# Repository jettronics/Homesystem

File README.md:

# Homesystem

## Introduction
The Homesystem project has been created to provide web radio stream for different rooms. Which can be controlled by Alexa, by Smart Phone and by a Remote controller centrally.
Further more the Homesystem acts as an Alarm center to monitor different sensors like water sensor to protect for water damage. In case of an Alarm the Homesystem can send Push Messages to a Smart Phone.

## Overview
The Homesystem centeral unit is realized by a Raspberry PI 3B+ controller module. 

Radio can be played by Loudspeakers installed in different rooms of the appartment. Controlling the radio streams can be happened by different ways
* Alexa - The speech command for radio streaming is routed over Alexa to the Central unit. 
* Smart Phone - A browser interface is provided by NodeRED
* Remote Controller - A FM based controller to control the radio player on Central unit.

With the MPD (Music Player Daemon) player running on Central unit a list of radio streaming provides can be selected.  
Sensors detect water flowing accidentally on floor. Sensor Alarm messages are routed by a FM (433MHz) link between Sensor and Central unit.
In case of water detection push messages will be sent which can be received and read on Smartphone.
For further technical details see Wiki page.
## Operation
The User can interact with the Homesystem over Alexa Speech Commands, Smart Phone Interface and Remote Controller.
### Alexa Speech Commands
Node RED uses amazon-echo-device-nodes to receive speech commands from Alexa. For Alexa those nodes are visible as a Light Bulb and can be speech controlled accordingly.
Following Speech Commands are available:
* Radio Küche
* Radio Bad
* Lieblingssender
* Was anderes
* Radio lauter
* Radio leiser

To activate webradio in kitchen say e.g. "Alexa, schalte Radio Küche ein!"
### Smart Phone Interface
There are two tabs as Interface to Homesystem.  
The first one is to control Webradio with different stations.  

The next tab shows the status of the different Watersensors.  

Green LED means no water detected. Red LED means water detected. In case of Water detection a Push message will be sent to Smart Phone.
### Remote Controller
The Remote Controller is a small device to control Webradio by 4 buttons.
* On/Off Webradio
* Next Webradio station
* Volume up
* Volume down
  
### Water Detection
This sensor device detects water and sends an appropiate signal to Homesystem centrals unit. 
The Homesystem acts as a gateway and sends push messages on registered Smart phones in case of water detected. 
The sensor draws very less standby current so that the battery can be used a very long time.

## Improvements
- [x] HF Transmission for Remote Controller just Parity Bit checked. For more robust transmission a CRC check or similiar check can be used.
- [x] Loud speaker announcement for the Webradio channel when changing the Webradio channel over e.g. Speech commands.

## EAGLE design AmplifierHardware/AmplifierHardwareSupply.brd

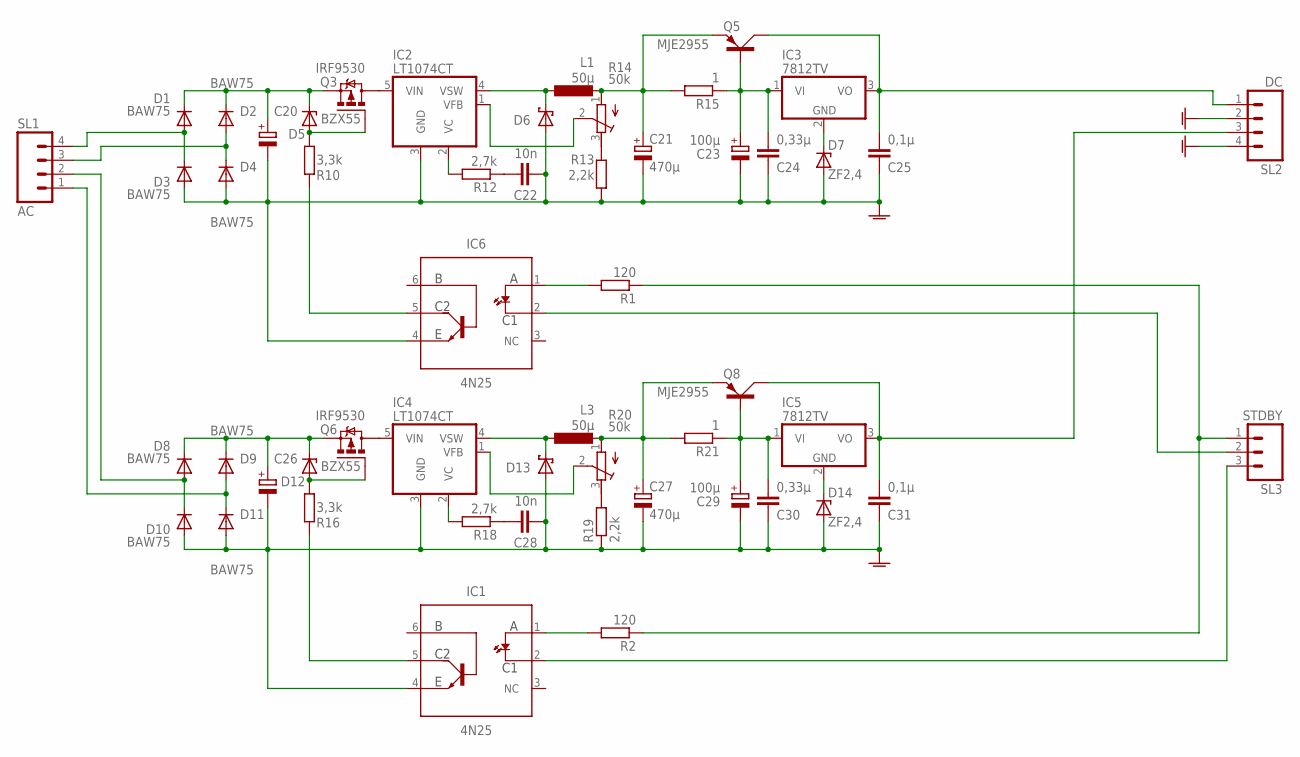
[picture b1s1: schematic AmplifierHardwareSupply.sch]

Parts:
C20, C26: CPOL-EUE5-10.5; E5-10,5
C21, C27: 470µ; E5-10,5
C22, C28: 10n; C025-024X044
C23, C29: 100µ; E5-10,5
C24, C30: 0,33µ; C025-024X044
C25, C31: 0,1µ; C025-024X044
D1, D2, D3, D4, D8, D9, D10, D11: BAW75; DO35-10
D5, D12: BZX55; DO35Z10
D6, D13: SCHOTTKY-DIODEDO35-7; DO35-7
D7, D14: ZF2,4; DO34Z7
IC1, IC6: 4N25; DIP762W60P254L712H480Q6B
IC2, IC4: LT1074CT; TO220-5
IC3, IC5: 7812TV; TO220V
L1, L3: 50µ; TJ3-U1
Q3, Q6: IRF9530; TO220BV
Q5, Q8: MJE2955; TO220AV
R1, R2: 120; 0207/2V
R10, R16: 3,3k; 0207/2V
R12, R18: 2,7k; 0207/2V
R13, R19: 2,2k; 0207/2V
R14, R20: 50k; RTRIM64W
R15, R21: 1; 0207/2V
SL1: AC; 04P
SL2: DC; 04P
SL3: STDBY; 03P

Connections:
+UB2: C31.2, IC5.3 (VO), Q8.C, SL2.3
AGND: C20.-, C21.-, C22.2, C23.-, C24.1, C25.1, C26.-, C27.-, C28.2, C29.-, C30.1, C31.1, D3.A, D4.A, D6.A, D7.A, D10.A, D11.A, D13.A, D14.A, IC1.4 (E), IC2.3 (GND), IC4.3 (GND), IC6.4 (E), R13.1, R19.1, SL2.2, SL2.4
unnamed: C25.2, IC3.3 (VO), Q5.C, SL2.1
unnamed: R1.1, R2.1, SL3.1
unnamed: IC6.1 (A), R1.2
unnamed: IC1.1 (A), R2.2
unnamed: IC6.2 (C1), SL3.2
unnamed: IC1.2 (C1), SL3.3
unnamed: IC2.2 (VC), R12.2
unnamed: R13.2, R14.3 (A)
unnamed: D1.A, D3.C, SL1.4
unnamed: IC4.2 (VC), R18.2
unnamed: IC2.5 (VIN), Q3.D
unnamed: D5.A, Q3.G, R10.2
unnamed: IC6.5 (C2), R10.1
unnamed: C21.+, L1.2, Q5.E, R14.1 (E), R15.2
unnamed: C22.1, R12.1
unnamed: D6.C, IC2.4 (VSW), L1.1
unnamed: IC2.1 (VFB), R14.2 (S)
unnamed: D7.C, IC3.2 (GND)
unnamed: R19.2, R20.3 (A)
unnamed: C23.+, C24.2, IC3.1 (VI), Q5.B, R15.1
unnamed: D8.A, D10.C, SL1.2
unnamed: D9.A, D11.C, SL1.1
unnamed: C26.+, D8.C, D9.C, D12.C, Q6.S
unnamed: D12.A, Q6.G, R16.2
unnamed: IC1.5 (C2), R16.1
unnamed: C28.1, R18.1
unnamed: D13.C, IC4.4 (VSW), L3.1
unnamed: IC4.5 (VIN), Q6.D
unnamed: C27.+, L3.2, Q8.E, R20.1 (E), R21.2
unnamed: IC4.1 (VFB), R20.2 (S)
unnamed: C29.+, C30.2, IC5.1 (VI), Q8.B, R21.1
unnamed: D14.C, IC5.2 (GND)
unnamed: C20.+, D1.C, D2.C, D5.C, Q3.S
unnamed: D2.A, D4.C, SL1.3

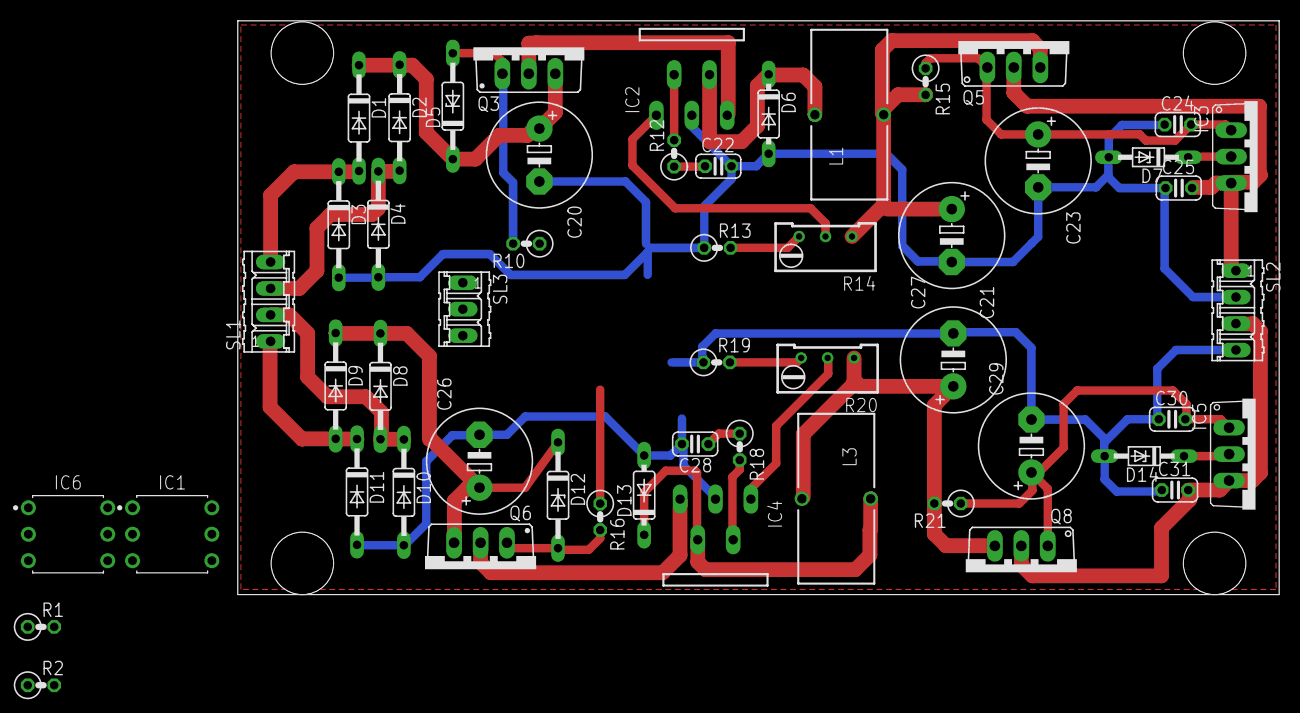
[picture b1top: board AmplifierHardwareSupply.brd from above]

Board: 2 copper layers, 100.0 x 55.1 mm, 53 parts (0 on the bottom side), 36 nets.

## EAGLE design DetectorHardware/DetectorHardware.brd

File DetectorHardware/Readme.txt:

RATS in board command line to fill polygon

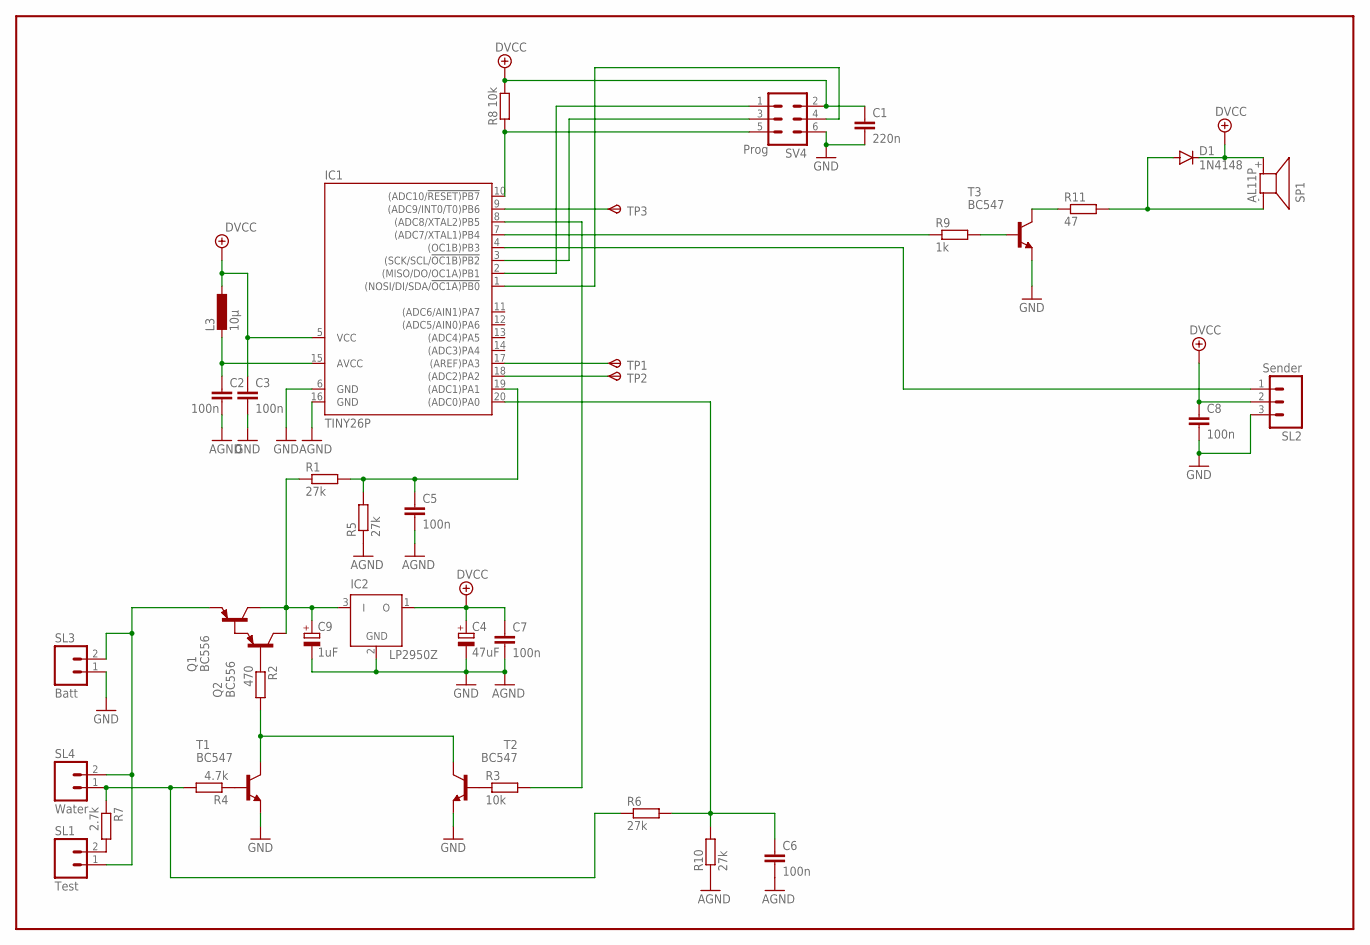
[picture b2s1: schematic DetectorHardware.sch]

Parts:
C1: 220n; C025-024X044
C2, C3, C5, C6, C7, C8: 100n; C025-024X044
C4: 47uF; E2,5-6
C9: 1uF; E2,5-6
D1: 1N4148; D-5
IC1: TINY26P; DIL20
IC2: LP2950Z; TO92
L3: 10µ; 0204/5
Q1, Q2: BC556; TO92-EBC
R1, R5, R6, R10: 27k; 0204/5
R2: 470; 0204/5
R3, R8: 10k; 0204/5
R4: 4.7k; 0204/5
R7: 2.7k; 0204/5
R9: 1k; 0204/5
R11: 47; 0204/5
SL1: Test; 02P
SL2: Sender; 03P
SL3: Batt; 02P
SL4: Water; 02P
SP1: AL11P
SV4: Prog; MA03-2
T1, T2, T3: BC547; TO92
TP1, TP2, TP3: TPSB1,27; B1,27

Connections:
+5V: C1.1, C3.1, C4.+, C7.1, C8.1, D1.C, IC1.5 (VCC), IC2.1 (O), L3.1, R8.2, SL2.2, SP1.+ (2), SV4.2
GND: C1.2, C2.2, C3.2, C4.-, C5.2, C6.2, C7.2, C8.2, C9.-, IC1.6 (GND), IC1.16 (GND), IC2.2 (GND), R5.1, R10.1, SL2.3, SL3.1, SV4.6, T1.1 (E), T2.1 (E), T3.1 (E)
unnamed: IC1.17 ((AREF)PA3), TP1.TP
unnamed: R7.2, SL1.2
unnamed: C5.1, IC1.19 ((ADC1)PA1), R1.2, R5.2
unnamed: C2.1, IC1.15 (AVCC), L3.2
unnamed: R9.2, T3.2 (B)
unnamed: R4.1, T1.2 (B)
unnamed: Q1.B, Q2.E
unnamed: R2.2, T1.3 (C), T2.3 (C)
unnamed: R3.1, T2.2 (B)
unnamed: C6.1, IC1.20 ((ADC0)PA0), R6.2, R10.2
unnamed: IC1.8 ((ADC8/XTAL2)PB5), R3.2
unnamed: IC1.18 ((ADC2)PA2), TP2.TP
unnamed: R4.2, R6.1, R7.1, SL4.1
unnamed: IC1.2 ((MISO/DO/OC1A)PB1), SV4.1
unnamed: Q1.E, SL1.1, SL3.2, SL4.2
unnamed: D1.A, R11.2, SP1.- (1)
unnamed: IC1.4 ((OC1B)PB3), SL2.1
unnamed: IC1.7 ((ADC7/XTAL1)PB4), R9.1
unnamed: IC1.10 ((ADC10/!RESET)PB7), R8.1, SV4.5
unnamed: IC1.3 ((SCK/SCL/!OC1B)PB2), SV4.3
unnamed: IC1.1 ((NOSI/DI/SDA/!OC1A)PB0), SV4.4
unnamed: IC1.9 ((ADC9/INT0/T0)PB6), TP3.TP
unnamed: C9.+, IC2.3 (I), Q1.C, Q2.C, R1.1
unnamed: Q2.B, R2.1
unnamed: R11.1, T3.3 (C)

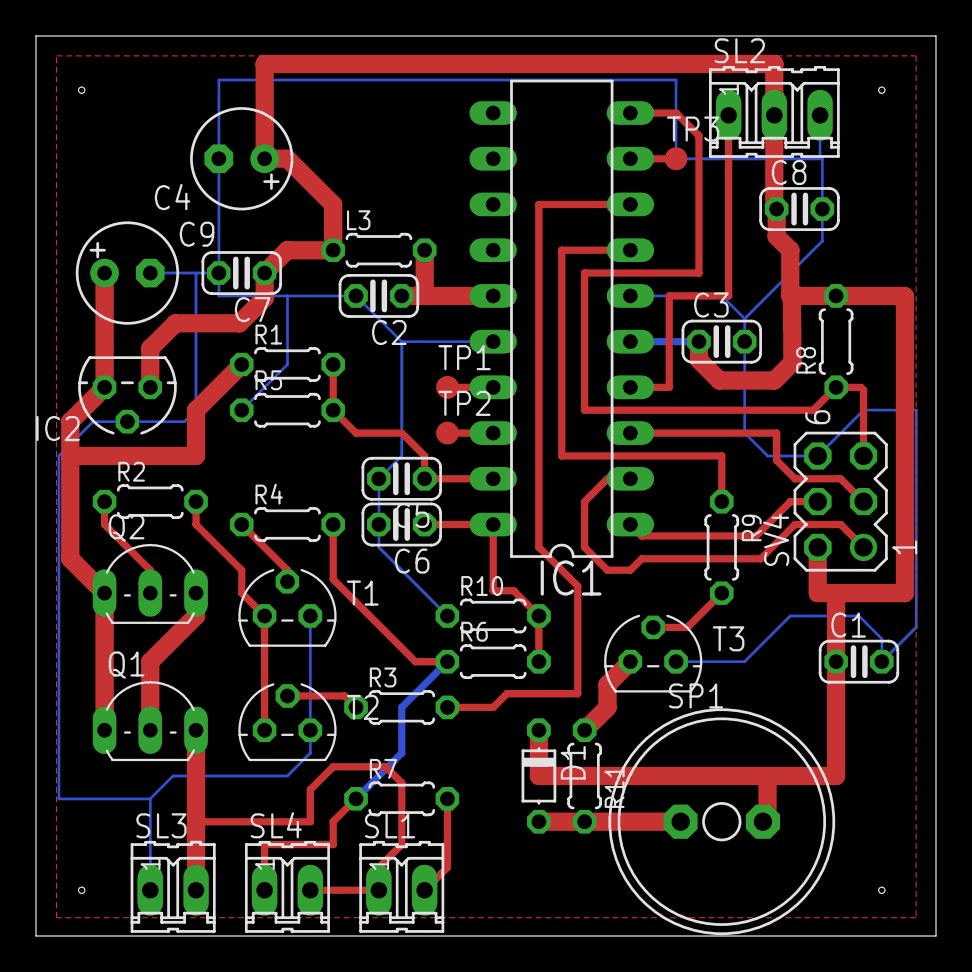
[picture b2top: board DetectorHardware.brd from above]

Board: 2 copper layers, 50.0 x 50.0 mm, 38 parts (0 on the bottom side), 27 nets.

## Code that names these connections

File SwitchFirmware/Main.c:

/*
 * Created: 09.02.2019 10:48:31
 * Author : Jens
 */ 

#include <avr/io.h>
#include <avr/interrupt.h>

#include "Types.h"

#include "Timer.h"
#include "Receive.h"
#include "Io.h"
#include "Control.h"



static void avr_init(void);


int main(void)
{
	avr_init();

	Receive_Init();
	Timer_Init();
	Control_Init();

	Receive_Register(Control_Event);

	sei();

	while( 1 )
	{
		// Tasks here.
	   Receive_Process();
		Control_Process();
	}

	return(0);
}


static void avr_init(void)
{
	// Initialize device here.

	// Pull up resistor activation set PORTXn to 1 if configured as input

	//Dev   Dev   Dev   Dev   TP1   TP2    Batt  Detect
	//PA7   PA6   PA5   PA4   PA3   PA2   PA1   PA0
	// I     I     I     I     O     O     I     I
	// 0     0     0     0     1     1     0     0
	DDRA = 0x0C;
	// 1     1     1     1     0     0     0     0
	PORTA = 0xF0;

	//Reset TP3   Pow   Snd   HF1   nc    nc    nc
	//PB7   PB6   PB5   PB4   PB3   PB2   PB1   PB0
	// I     O     O     O     O     I     I     I
	// 0     1     1     1     1     0     0     0
	DDRB = 0x78;
	// 0     0     1     0     0     1     1     1
	PORTB = 0x27;

	// Enable and lock PLL
	PLLCSR |= _BV(PLLE);

	// Wait for PLL to lock (app. 100 ms)
	while( !(PLLCSR & _BV(PLOCK)) )
	{
		;
	}

	return;
}

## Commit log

2021-04-11 Create ServerSoftware
2021-11-01 All missing Firmware, Hardware folders added
2021-11-06 Images moved to Images folder
2021-11-21 Server Software and Server Hardware documentation
2021-11-21 EA project
2021-11-23 Screenshots added
2021-11-23 Images added
2021-12-03 Amplifier Hardware Schematic
2021-12-03 Server Hardware Schematic renamed
2021-12-04 HF Receiver and Transmitter Images
2021-12-05 Speech to text webradio
2021-12-12 State Machine Server Firmware
2021-12-12 Detector Firmware State Machine
2021-12-13 Webradio station announcement
2022-07-24 Overview image and powerpoint
2023-07-06 Parity replaced by CRC code
2023-07-07 Compare check removed, Parity check by Syndrom decoding replaced
2023-07-07 Parity and CRC coding separated by different files
2023-07-07 Transmit crc
2023-07-08 ServerFirmware crc draft version
2023-07-22 All Firmwares updated due to CRC check
2024-05-31 Files added
2024-05-31 Files removed
2026-01-29 Images split
2026-02-19 Voltage Supply
2026-02-24 Supply Voltage schematic adapted
2026-02-24 Supply Voltage image adapted
